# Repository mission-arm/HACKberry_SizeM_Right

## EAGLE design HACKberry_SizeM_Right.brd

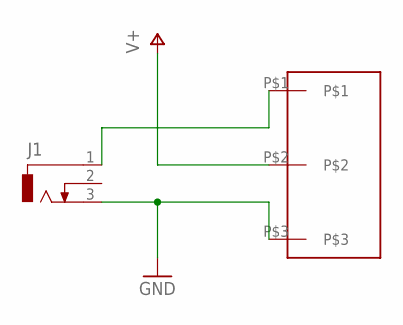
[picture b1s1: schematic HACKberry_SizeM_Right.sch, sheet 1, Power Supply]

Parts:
J1: DCJ0303
U$2: SS-12D00

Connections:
GND: J1.3, U$2.P$3; also elsewhere on the board
unnamed: J1.1, U$2.P$1
V+: U$2.P$2; also elsewhere on the board

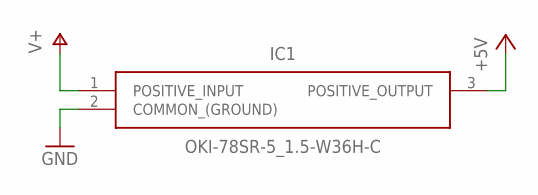
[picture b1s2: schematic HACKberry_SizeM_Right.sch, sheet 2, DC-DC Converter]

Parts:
IC1: OKI-78SR-5_1.5-W36H-C; OKI-78SR-HORIZONTAL

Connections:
+5V: IC1.3 (POSITIVE_OUTPUT); also elsewhere on the board
GND: IC1.2 (COMMON_(GROUND)); also elsewhere on the board
V+: IC1.1 (POSITIVE_INPUT); also elsewhere on the board

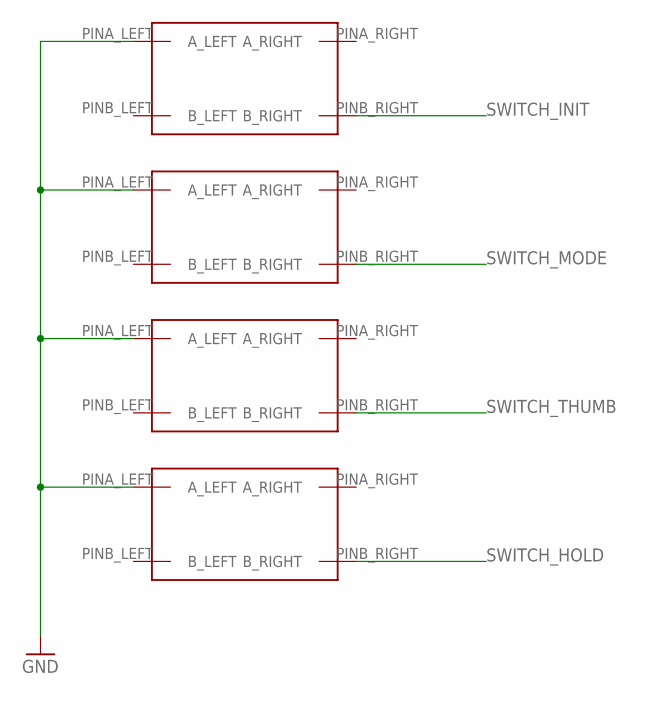
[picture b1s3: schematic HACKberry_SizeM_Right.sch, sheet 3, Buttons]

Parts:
U$1, U$3, U$4, U$5: SKRPACE010

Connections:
GND: U$1.PINA_LEFT (A_LEFT), U$3.PINA_LEFT (A_LEFT), U$4.PINA_LEFT (A_LEFT), U$5.PINA_LEFT (A_LEFT); also elsewhere on the board
SWITCH_HOLD: U$5.PINB_RIGHT (B_RIGHT); also elsewhere on the board
SWITCH_INIT: U$1.PINB_RIGHT (B_RIGHT); also elsewhere on the board
SWITCH_MODE: U$3.PINB_RIGHT (B_RIGHT); also elsewhere on the board
SWITCH_THUMB: U$4.PINB_RIGHT (B_RIGHT); also elsewhere on the board

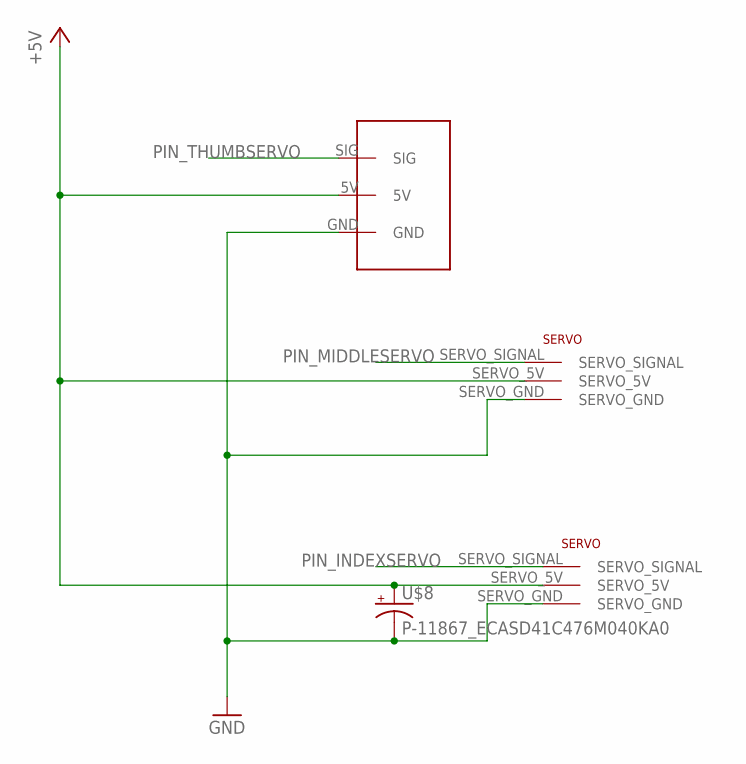
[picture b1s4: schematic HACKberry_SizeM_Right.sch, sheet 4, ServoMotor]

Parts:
INDEXPIN: NN_SERVO
MIDDLEPIN: NN_SERVO
THUMBPIN: 53047-0310_SERVO
U$8: P-11867_ECASD41C476M040KA0; ECASD41C476M040KA0

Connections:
+5V: INDEXPIN.SERVO_5V, MIDDLEPIN.SERVO_5V, THUMBPIN.5V, U$8.+; also elsewhere on the board
GND: INDEXPIN.SERVO_GND, MIDDLEPIN.SERVO_GND, THUMBPIN.GND, U$8.-; also elsewhere on the board
PIN_INDEXSERVO: INDEXPIN.SERVO_SIGNAL; also elsewhere on the board
PIN_MIDDLESERVO: MIDDLEPIN.SERVO_SIGNAL; also elsewhere on the board
PIN_THUMBSERVO: THUMBPIN.SIG; also elsewhere on the board

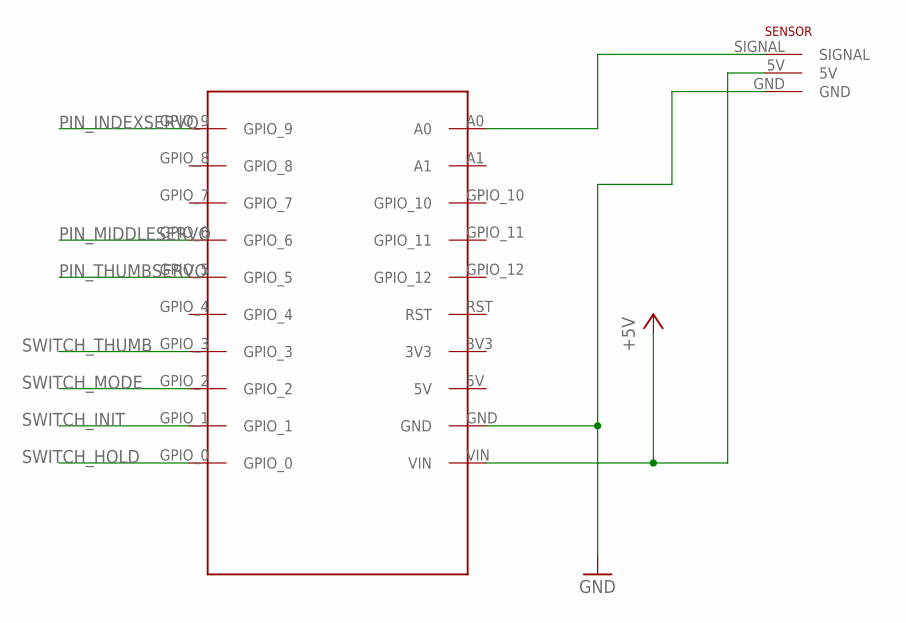
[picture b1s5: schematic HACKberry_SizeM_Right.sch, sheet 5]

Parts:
U$6: POLOLU_A_STAR_32U4_MICRO
U$7: NN_SENSOR

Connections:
+5V: U$6.VIN, U$7.5V; also elsewhere on the board
GND: U$6.GND, U$7.GND; also elsewhere on the board
unnamed: U$6.A0, U$7.SIGNAL
PIN_INDEXSERVO: U$6.GPIO_9; also elsewhere on the board
PIN_MIDDLESERVO: U$6.GPIO_6; also elsewhere on the board
PIN_THUMBSERVO: U$6.GPIO_5; also elsewhere on the board
SWITCH_HOLD: U$6.GPIO_0; also elsewhere on the board
SWITCH_INIT: U$6.GPIO_1; also elsewhere on the board
SWITCH_MODE: U$6.GPIO_2; also elsewhere on the board
SWITCH_THUMB: U$6.GPIO_3; also elsewhere on the board

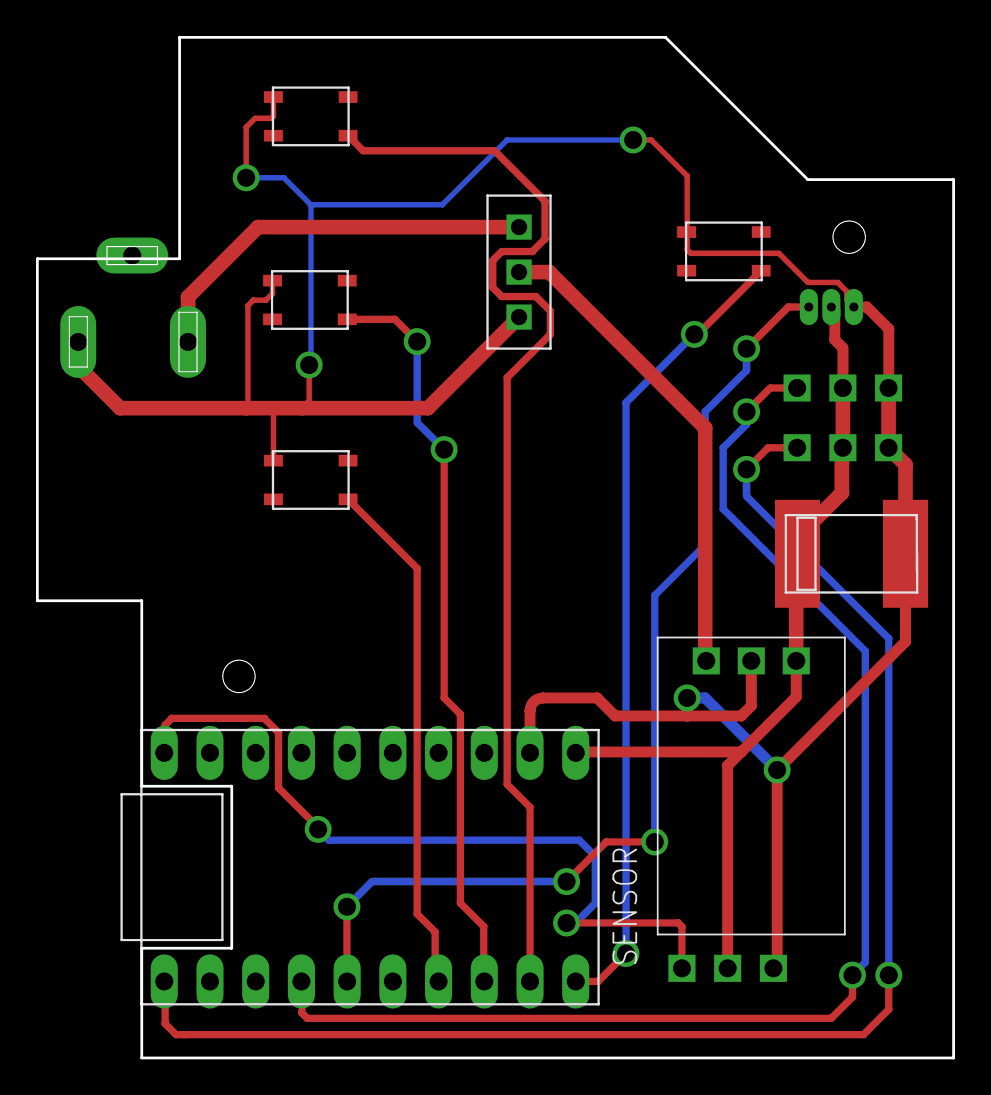
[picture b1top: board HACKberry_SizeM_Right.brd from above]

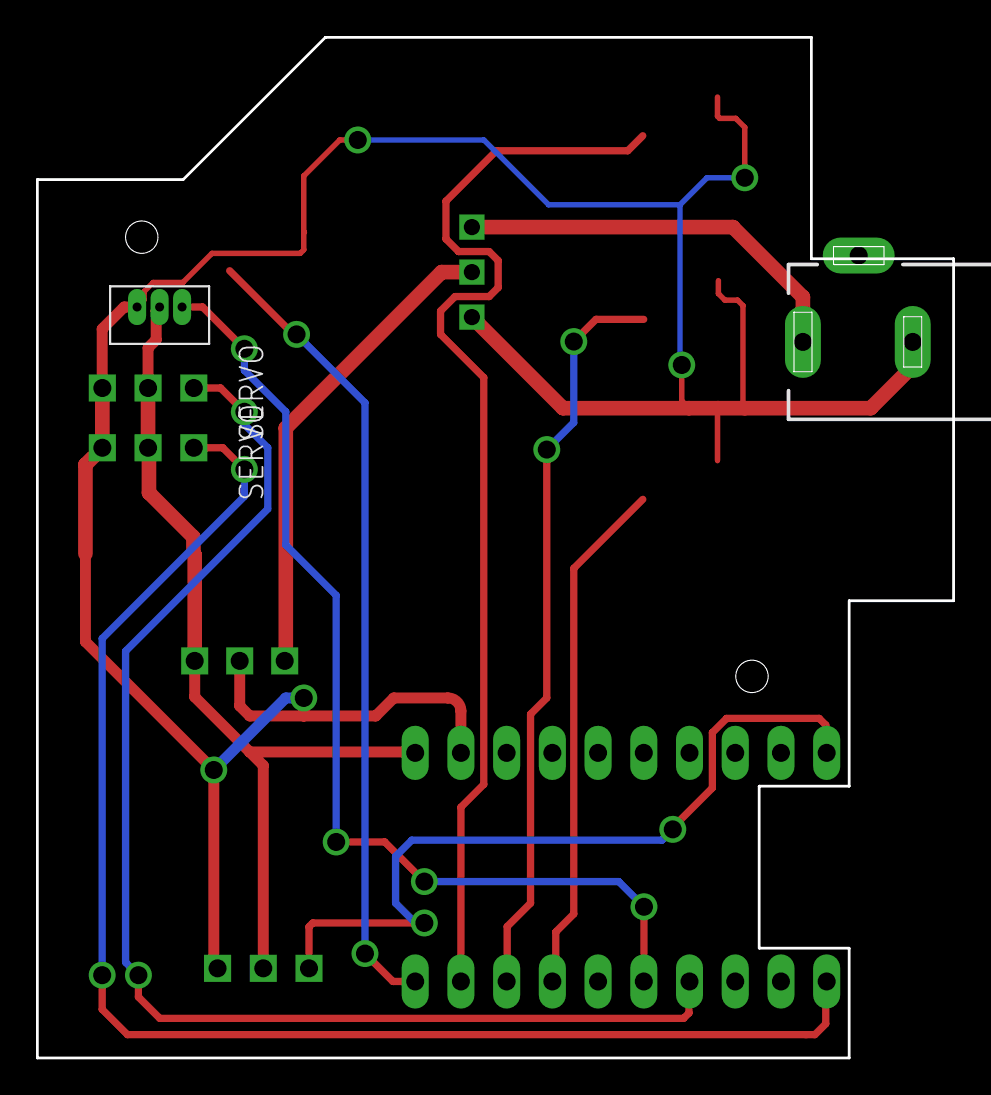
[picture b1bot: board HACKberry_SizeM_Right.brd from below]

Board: 2 copper layers, 50.9 x 56.7 mm, 13 parts (4 on the bottom side), 12 nets.

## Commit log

2017-10-14 rev 1
2017-10-14 rev1.1
2017-10-25 ポリスイッチを取り除き, サーボの電源ラインにパスコンを追加した.
2017-10-31 8milのDRUに対応
